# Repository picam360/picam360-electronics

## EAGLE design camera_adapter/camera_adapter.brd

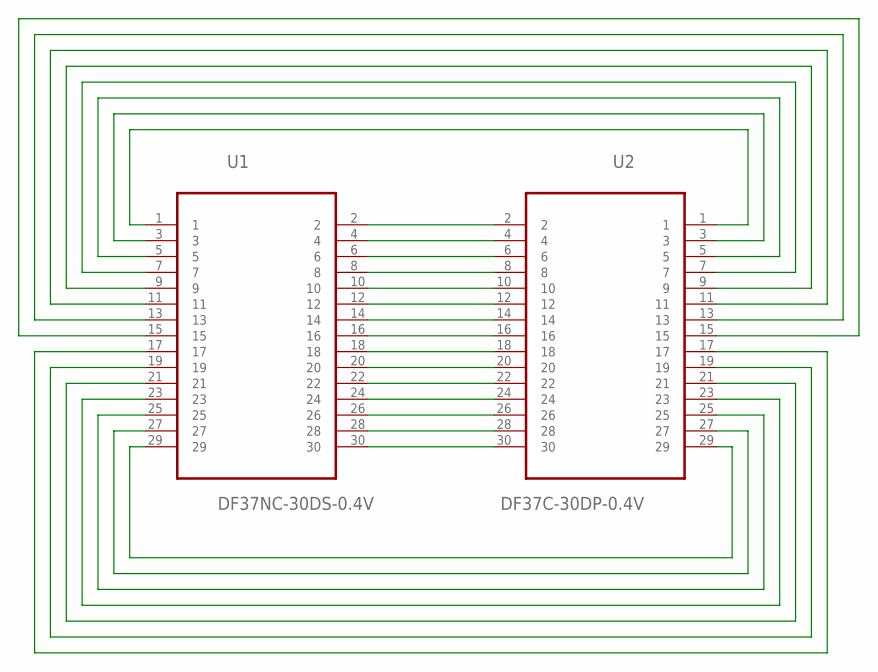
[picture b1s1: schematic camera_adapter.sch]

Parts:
U1: DF37NC-30DS-0.4V; DF37**-30DS-0.4V
U2: DF37C-30DP-0.4V; DF37**-30DP-0.4V

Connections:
unnamed: U1.2, U2.2
unnamed: U1.4, U2.4
unnamed: U1.6, U2.6
unnamed: U1.8, U2.8
unnamed: U1.10, U2.10
unnamed: U1.12, U2.12
unnamed: U1.14, U2.14
unnamed: U1.16, U2.16
unnamed: U1.18, U2.18
unnamed: U1.20, U2.20
unnamed: U1.22, U2.22
unnamed: U1.24, U2.24
unnamed: U1.26, U2.26
unnamed: U1.28, U2.28
unnamed: U1.30, U2.30
unnamed: U1.1, U2.1
unnamed: U1.3, U2.3
unnamed: U1.5, U2.5
unnamed: U1.7, U2.7
unnamed: U1.9, U2.9
unnamed: U1.11, U2.11
unnamed: U1.13, U2.13
unnamed: U1.15, U2.15
unnamed: U1.29, U2.29
unnamed: U1.27, U2.27
unnamed: U1.25, U2.25
unnamed: U1.23, U2.23
unnamed: U1.21, U2.21
unnamed: U1.19, U2.19
unnamed: U1.17, U2.17

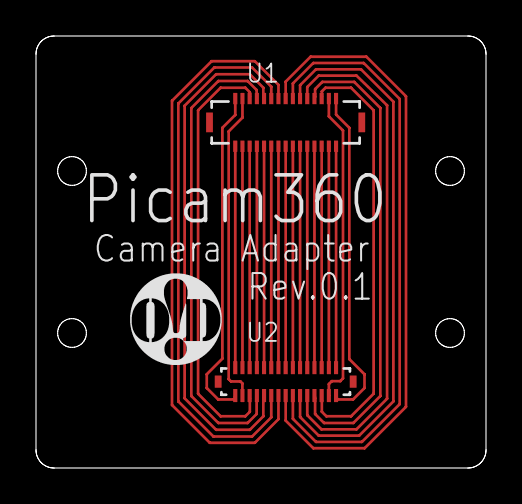
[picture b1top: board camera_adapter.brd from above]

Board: 2 copper layers, 25.0 x 24.0 mm, 3 parts (0 on the bottom side), 30 nets.

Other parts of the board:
LOGO1: OHMYDIGIFAB_LOGO

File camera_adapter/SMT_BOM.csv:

Component ID,Comment,Designator,Footprint,Pins,Quantity,DF37NC-30DS-0.4V,U1,,30,1,DF37C-30DP-0.4V,U2,,30,1

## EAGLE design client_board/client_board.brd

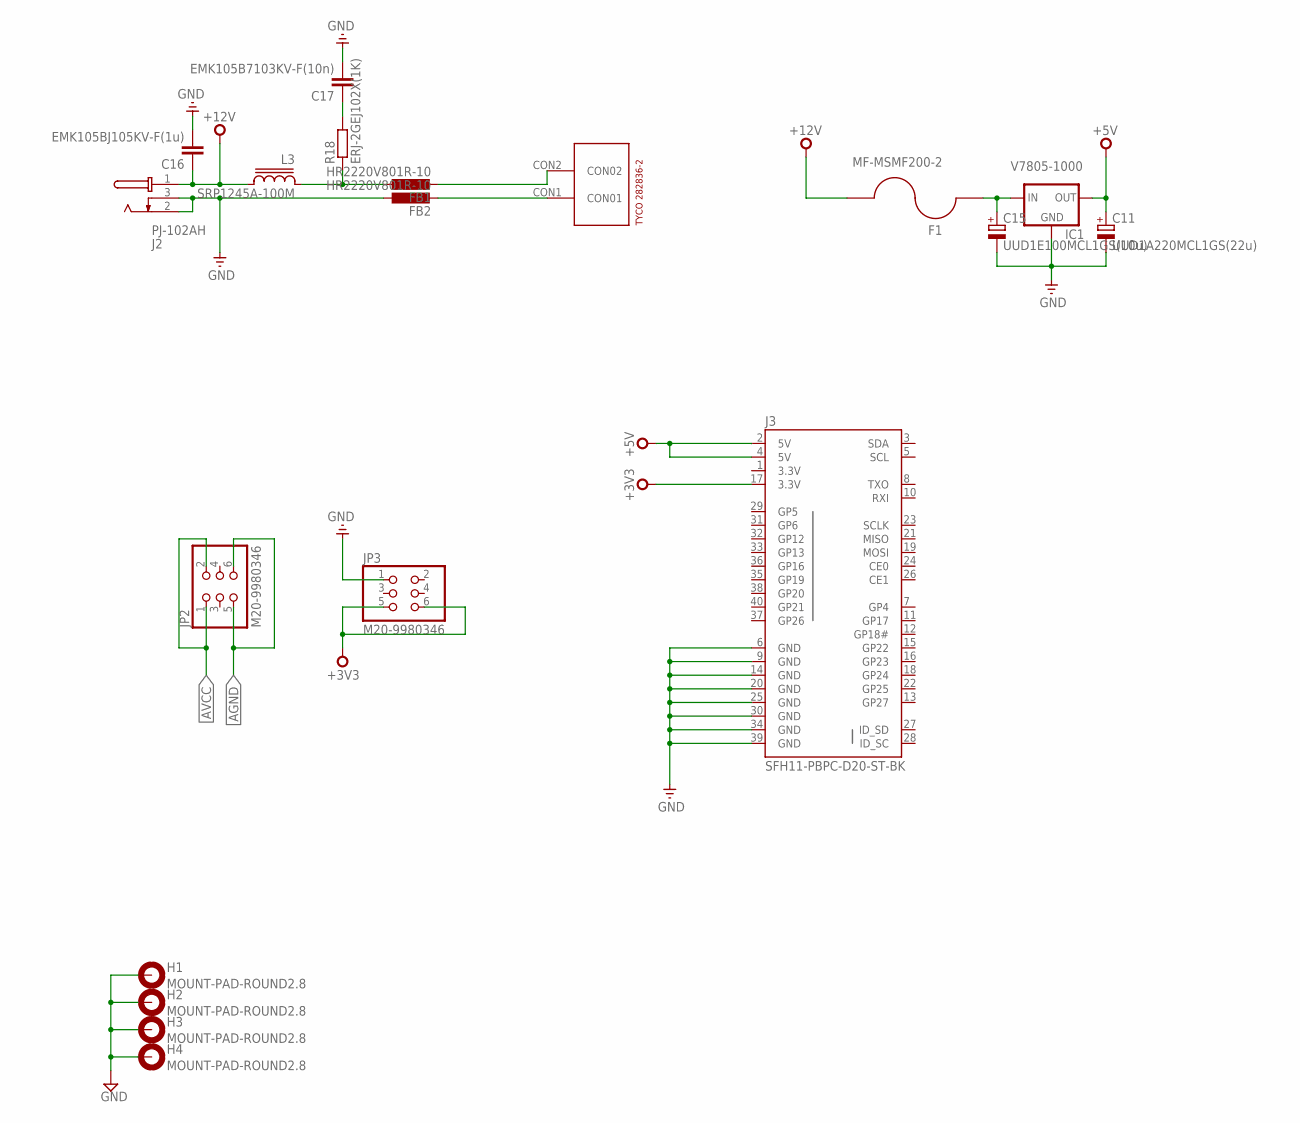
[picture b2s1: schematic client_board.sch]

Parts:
C11: UUD1A220MCL1GS(22u); 153CLV-0405
C15: UUD1E100MCL1GS(10u); 153CLV-0405
C16: EMK105BJ105KV-F(1u); C0402
C17: EMK105B7103KV-F(10n); C0402
F1: MF-MSMF200-2; 1812
FB1, FB2: HR2220V801R-10; L5650M
H1, H2, H3, H4: MOUNT-PAD-ROUND2.8; 2,8-PAD
IC1: V7805-1000; DIP_3PIN
J2: PJ-102AH; PJ-102XH
J3: SFH11-PBPC-D20-ST-BK; 2X20-SHROUDED
JP2, JP3: M20-9980346; 2X03
L3: SRP1245A-100M; SRP1250A
R18: ERJ-2GEJ102X(1K); R0402
U$1: 282836-2

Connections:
3.3V: J3.1 (3.3V)
+3V3: J3.17 (3.3V), JP3.5, JP3.6
+5V: C11.+, IC1.OUT, J3.2 (5V), J3.4 (5V)
+12V: C16.1, F1.1, J2.1 (T), L3.2
AGND: FB2.2, JP2.5, JP2.6, U$1.CON1 (CON01)
AVCC: FB1.2, JP2.1, JP2.2, U$1.CON2 (CON02)
GND: C11.-, C15.-, C16.2, C17.2, FB2.1, H1.B2,8, H2.B2,8, H3.B2,8, H4.B2,8, IC1.GND, J2.2 (S), J2.3 (SS), J3.6 (GND), J3.9 (GND), J3.14 (GND), J3.20 (GND), J3.25 (GND), J3.30 (GND), J3.34 (GND), J3.39 (GND), JP3.1
unnamed: C15.+, F1.2, IC1.IN
unnamed: FB1.1, L3.1, R18.1
unnamed: C17.1, R18.2

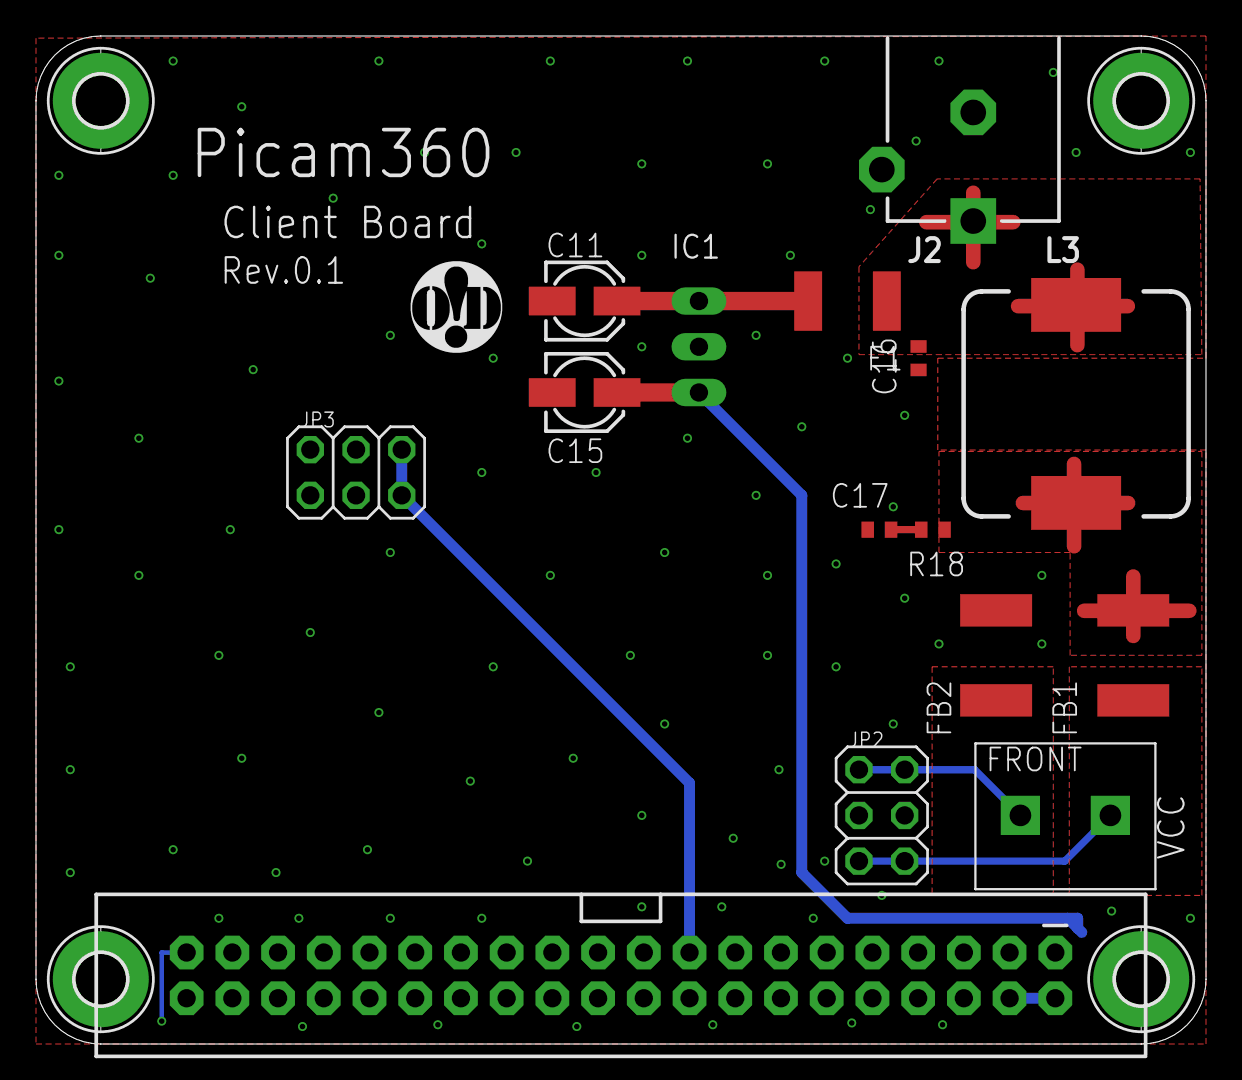
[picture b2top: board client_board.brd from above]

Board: 4 copper layers, 65.0 x 56.0 mm, 21 parts (0 on the bottom side), 9 nets.

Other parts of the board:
LOGO1: OHMYDIGIFAB_LOGO
U$2: TENDA_P200

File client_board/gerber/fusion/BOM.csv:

Part/Designator,Manufacture Part Number/Seeed SKU,QuantityC17,EMK105B7103KV-F,1C15,UUD1E100MCL1GS,1R18,ERJ-2GEJ102X,1C16,EMK105BJ105KV-F,1C11,UUD1A220MCL1GS,1U$1,282836-2,1F1,MF-MSMF200-2,1"FB1, FB2",HR2220V801R-10,2J2,PJ-102AH,1J3,SFH11-PBPC-D20-ST-BK,1L3,SRP1245A-100M,1"JP2, JP3",M20-9980346,2

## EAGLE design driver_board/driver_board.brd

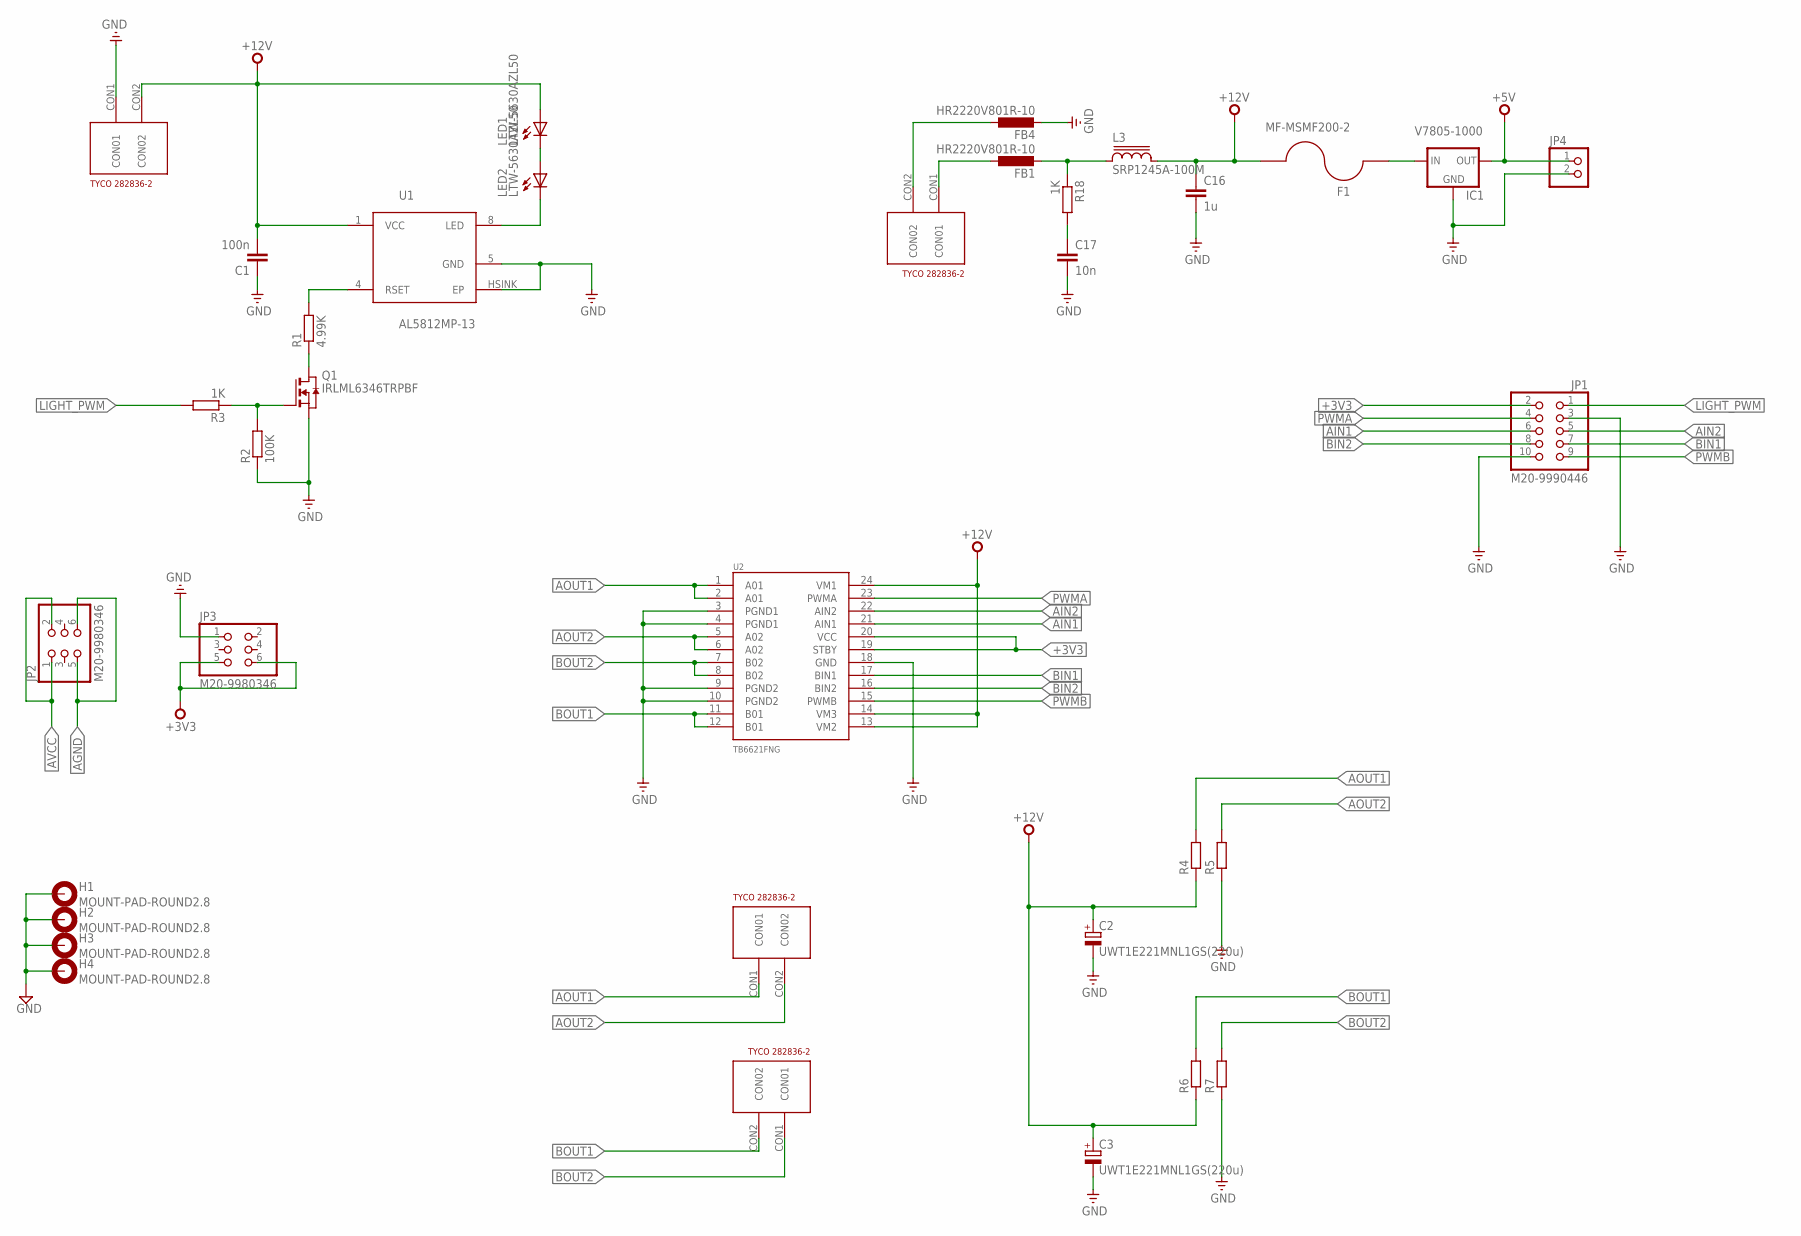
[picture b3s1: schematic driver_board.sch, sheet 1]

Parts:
C1: 100n; C0402
C2, C3: UWT1E221MNL1GS(220u); 153CLV-0810
C16: 1u; C0402
C17: 10n; C0402
F1: MF-MSMF200-2; 1812
FB1, FB4: HR2220V801R-10; L5650M
H1, H2, H3, H4: MOUNT-PAD-ROUND2.8; 2,8-PAD
IC1: V7805-1000; DIP_3PIN
JP1: M20-9990446; 2X05
JP2, JP3: M20-9980346; 2X03_SMT
JP4: PINHD-1X2; 1X02
L3: SRP1245A-100M; SRP1250A
LED1, LED2: LTW-5630AZL50; LITEON-5630
Q1: IRLML6346TRPBF; SOT23
R1: 4.99K; R0402
R2: 100K; R0402
R3, R18: 1K; R0402
R4, R5, R6, R7: R-EU_R0805; R0805
U1: AL5812MP-13; MSOP-8EP
U2: TB6621FNG; SSOP24
U$2, U$4, U$7, U$8: 282836-2

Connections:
+3V3: JP1.2, JP3.5, JP3.6, U2.19 (STBY), U2.20 (VCC)
+5V: IC1.OUT, JP4.1
+12V: C1.2, C2.+, C3.+, C16.1, F1.1, L3.2, LED1.A1 (A), LED1.A2 (A), LED1.A3 (A), R4.1, R6.1, U1.1 (VCC), U2.13 (VM2), U2.14 (VM3), U2.24 (VM1), U$4.CON2 (CON02)
AGND: FB4.1, JP2.5, JP2.6, U$2.CON2 (CON02)
AIN1: JP1.6, U2.21 (AIN1)
AIN2: JP1.5, U2.22 (AIN2)
AOUT1: R4.2, U2.1 (A01), U2.2 (A01), U$8.CON1 (CON01)
AOUT2: R5.2, U2.5 (A02), U2.6 (A02), U$8.CON2 (CON02)
AVCC: FB1.1, JP2.1, JP2.2, U$2.CON1 (CON01)
BIN1: JP1.7, U2.17 (BIN1)
BIN2: JP1.8, U2.16 (BIN2)
BOUT1: R6.2, U2.11 (B01), U2.12 (B01), U$7.CON2 (CON02)
BOUT2: R7.2, U2.7 (B02), U2.8 (B02), U$7.CON1 (CON01)
GND: C1.1, C2.-, C3.-, C16.2, C17.2, FB4.2, H1.B2,8, H2.B2,8, H3.B2,8, H4.B2,8, IC1.GND, JP1.3, JP1.10, JP3.1, JP4.2, Q1.2 (S), R2.1, R5.1, R7.1, U1.5 (GND), U1.HSINK (EP), U2.3 (PGND1), U2.4 (PGND1), U2.9 (PGND2), U2.10 (PGND2), U2.18 (GND), U$4.CON1 (CON01)
LIGHT_PWM: JP1.1, R3.2
unnamed: LED1.C1 (C), LED1.C2 (C), LED2.A1 (A), LED2.A2 (A), LED2.A3 (A)
unnamed: FB1.2, L3.1, R18.1
unnamed: R1.2, U1.4 (RSET)
unnamed: Q1.3 (D), R1.1
unnamed: Q1.1 (G), R2.2, R3.1
unnamed: LED2.C1 (C), LED2.C2 (C), U1.8 (LED)
unnamed: C17.1, R18.2
unnamed: F1.2, IC1.IN
PWMA: JP1.4, U2.23 (PWMA)
PWMB: JP1.9, U2.15 (PWMB)

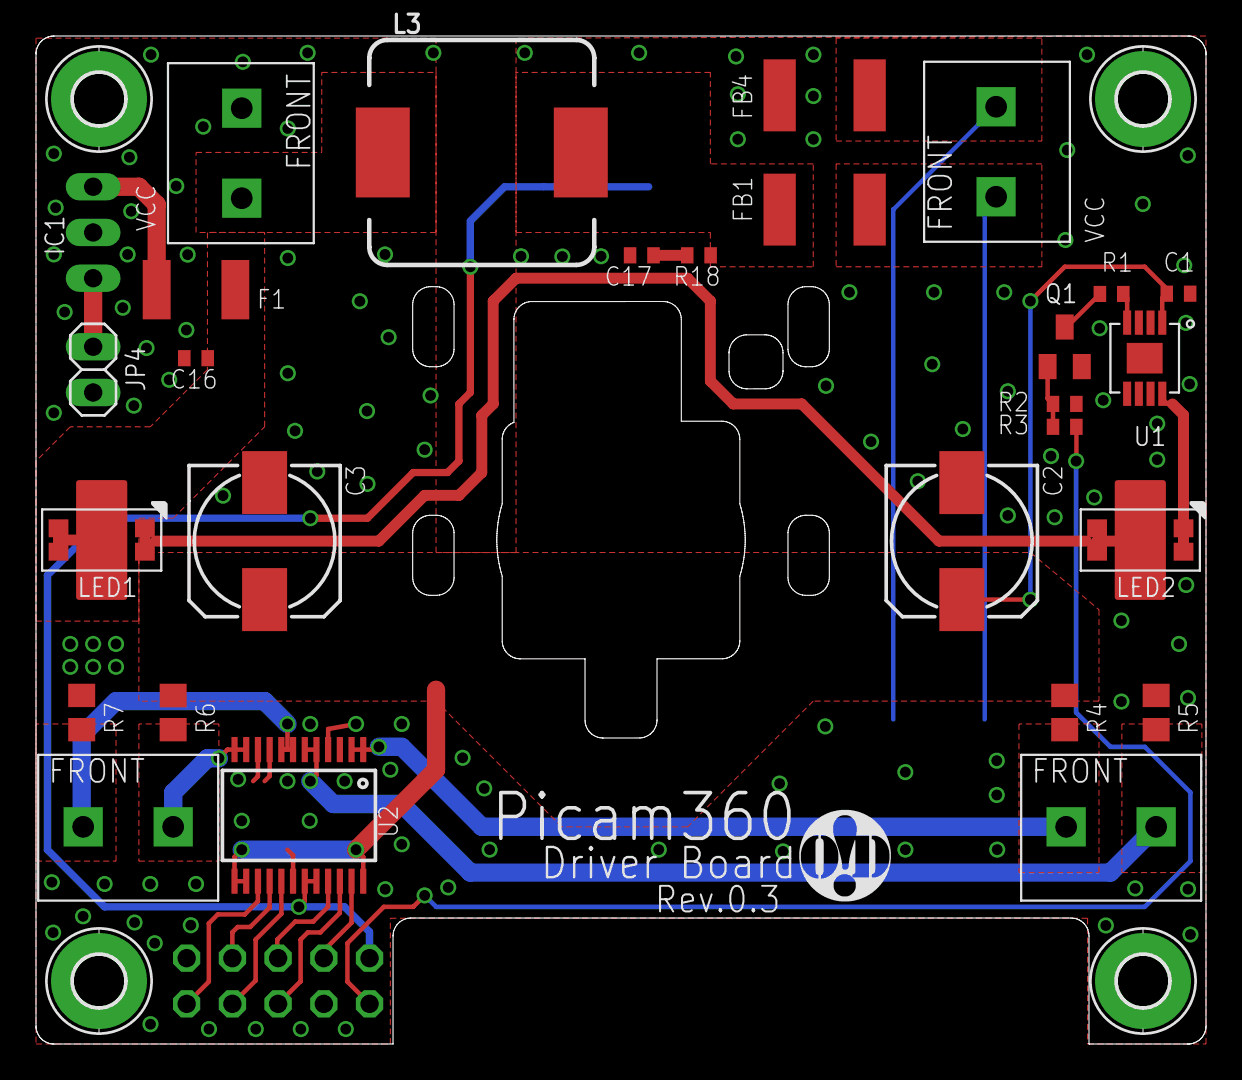
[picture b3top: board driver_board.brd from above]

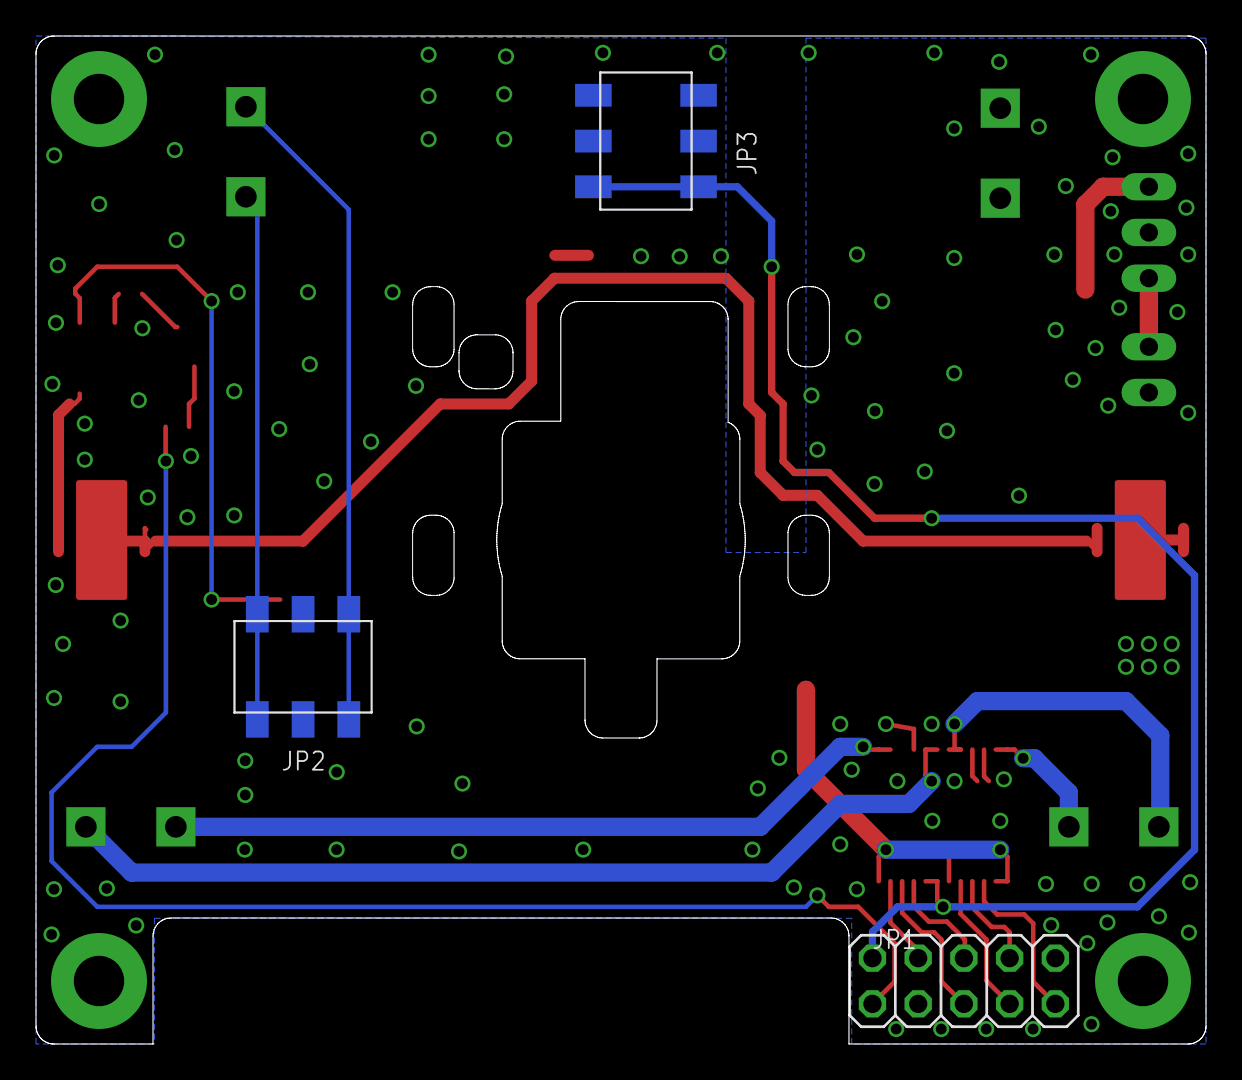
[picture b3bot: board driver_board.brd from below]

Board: 4 copper layers, 65.0 x 56.0 mm, 37 parts (4 on the bottom side), 25 nets.

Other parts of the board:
LOGO1: OHMYDIGIFAB_LOGO
U$3: TENDA_P200

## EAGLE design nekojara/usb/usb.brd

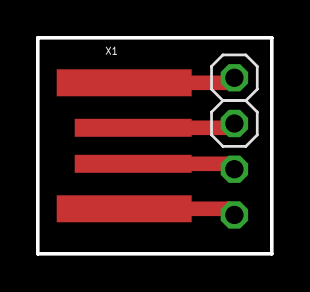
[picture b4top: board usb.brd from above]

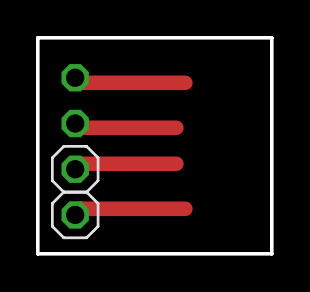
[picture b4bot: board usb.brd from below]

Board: 2 copper layers, 13.0 x 12.0 mm, 5 parts (2 on the bottom side), 4 nets.

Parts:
JP1, JP2, JP3, JP4: 1X01
X1: USBPCB; USB-A-PCB

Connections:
5V: JP3.1, X1.5V
GND: JP4.1, X1.GND
USB_N: JP2.1, X1.USB_M
USB_P: JP1.1, X1.USB_P

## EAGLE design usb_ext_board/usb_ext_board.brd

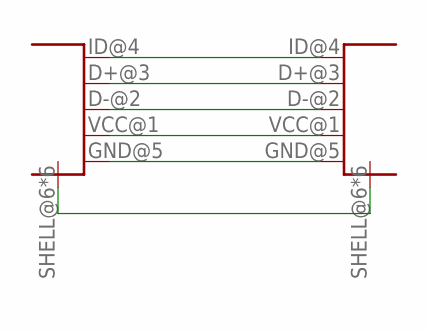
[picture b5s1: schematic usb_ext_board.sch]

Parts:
MALE1, MALE2: USB-ID; USB3150-30-130

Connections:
D+: MALE1.D+@3 (D+), MALE2.D+@3 (D+)
D-: MALE1.D-@2 (D-), MALE2.D-@2 (D-)
GND: MALE1.GND@5 (GND), MALE1.SHELL@6 (SHELL), MALE1.SHELL@7 (SHELL), MALE1.SHELL@8 (SHELL), MALE1.SHELL@9 (SHELL), MALE1.SHELL@10 (SHELL), MALE1.SHELL@11 (SHELL), MALE2.GND@5 (GND), MALE2.SHELL@6 (SHELL), MALE2.SHELL@7 (SHELL), MALE2.SHELL@8 (SHELL), MALE2.SHELL@9 (SHELL), MALE2.SHELL@10 (SHELL), MALE2.SHELL@11 (SHELL)
ID: MALE1.ID@4 (ID), MALE2.ID@4 (ID)
VCC: MALE1.VCC@1 (VBUS), MALE2.VCC@1 (VBUS)

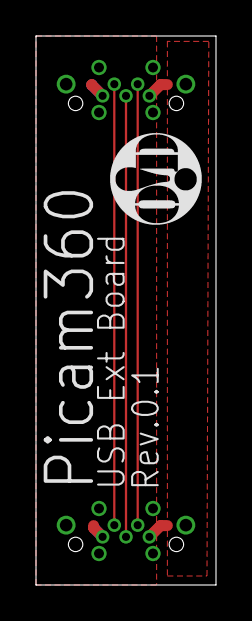
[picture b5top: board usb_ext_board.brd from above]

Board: 2 copper layers, 10.0 x 30.5 mm, 3 parts (0 on the bottom side), 5 nets.

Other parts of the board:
LOGO1: OHMYDIGIFAB_LOGO

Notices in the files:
parts and their libraries:
SparkFun-Boards: Licensing: Creative Commons ShareAlike 4.0 International - https://creativecommons.org/licenses/by-sa/4.0
con-dc-power: Copyright (C) 2015, Bob Starr
